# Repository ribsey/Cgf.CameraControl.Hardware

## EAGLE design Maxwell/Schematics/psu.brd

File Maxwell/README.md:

# Maxwell MP-101 electronics replacement
## Specifications
With this replacement your Maxwell PTZ head can do the following:
* smoother movement on low speeds (designed for moving while live)
* positioning
* VISCA control input
* LANC output
* variable power output for camera
* USB power output for HDMI to SDI converters (e.g. BlackmagicDesign Micro Converter HDMI to SDI)

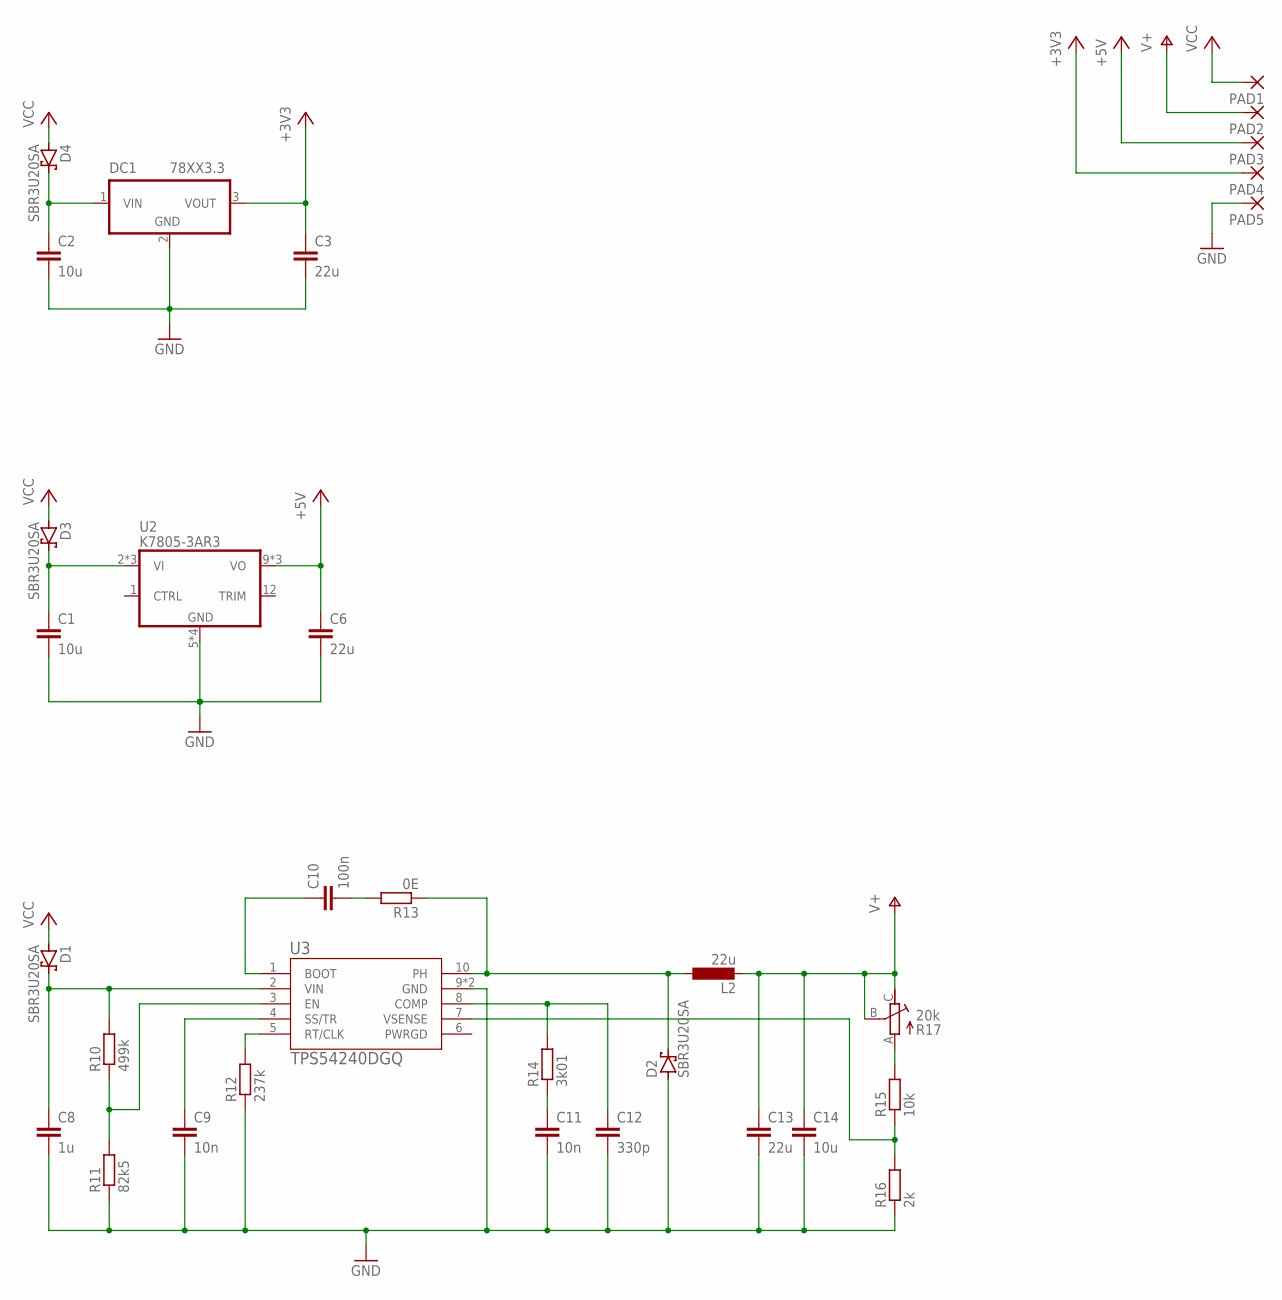
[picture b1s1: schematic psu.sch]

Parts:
C1, C2: 10u; C0805
C3, C6, C13: 22u; C0805
C8: 1u; C0805
C9, C11: 10n; C0603
C10: 100n; C0603
C12: 330p; C0603
C14: 10u; C0603
D1, D2, D3, D4: SBR3U20SA; SMA
DC1: 78XX3.3; SIP3
L2: 22u; ETQP4M
PAD1, PAD2, PAD3, PAD4, PAD5: WIREPAD2,54/1,1; 2,54/1,1
R10: 499k; R0603
R11: 82k5; R0603
R12: 237k; R0603
R13: 0E; R0603
R14: 3k01; R0603
R15: 10k; R0603
R16: 2k; R0603
R17: 20k; TS53YL
U2: K7805-3AR3; K78XX-3AR3
U3: TPS54240DGQ; HVSSOP-10P

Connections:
+3V3: C3.1, DC1.3 (VOUT), PAD4.1
+5V: C6.1, PAD3.1, U2.9 (VO), U2.10 (VO), U2.11 (VO)
GND: C1.2, C2.2, C3.2, C6.2, C8.2, C9.2, C11.2, C12.2, C13.2, C14.2, D2.A, DC1.2 (GND), PAD5.1, R11.1, R12.1, R16.1, U2.5 (GND), U2.6 (GND), U2.7 (GND), U2.8 (GND), U3.9 (GND), U3.11 (GND)
unnamed: C8.1, D1.C, R10.2, U3.2 (VIN)
unnamed: C1.1, D3.C, U2.2 (VI), U2.3 (VI), U2.4 (VI)
unnamed: C2.1, D4.C, DC1.1 (VIN)
unnamed: C11.1, R14.1
unnamed: C10.1, U3.1 (BOOT)
unnamed: C10.2, R13.2
unnamed: D2.C, L2.1, R13.1, U3.10 (PH)
unnamed: R15.1, R16.2, U3.7 (VSENSE)
unnamed: R10.1, R11.2, U3.3 (EN)
unnamed: C9.1, U3.4 (SS/TR)
unnamed: R12.2, U3.5 (RT/CLK)
unnamed: C12.1, R14.2, U3.8 (COMP)
unnamed: R15.2, R17.A
V+: C13.1, C14.1, L2.2, PAD2.1, R17.B (S), R17.C (E)
VCC: D1.A, D3.A, D4.A, PAD1.1

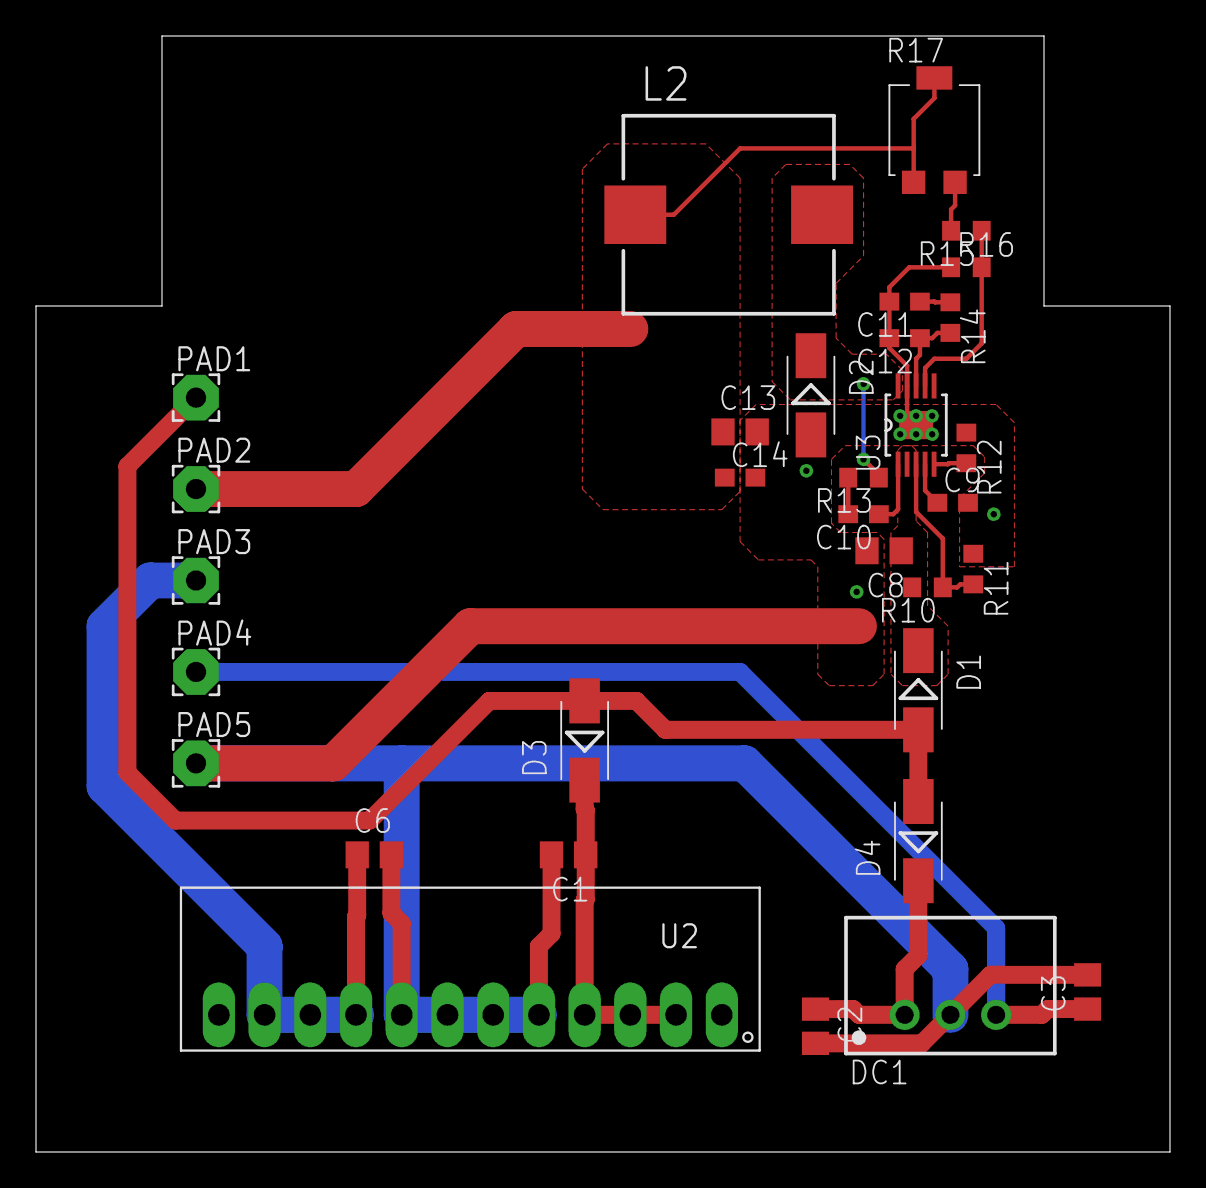
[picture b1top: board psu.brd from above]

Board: 2 copper layers, 63.0 x 62.0 mm, 32 parts (0 on the bottom side), 18 nets.

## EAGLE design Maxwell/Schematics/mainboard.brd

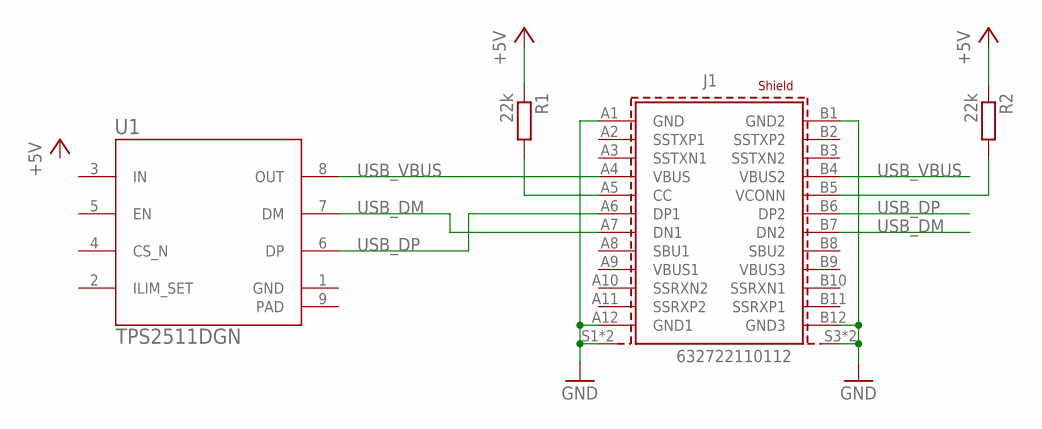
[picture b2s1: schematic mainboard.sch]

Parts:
J1: 632722110112
R1, R2: 22k; R0603
U1: TPS2511DGN; VSSOP-8P

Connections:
+5V: R1.1, R2.1
GND: J1.A1 (GND), J1.A12 (GND1), J1.B1 (GND2), J1.B12 (GND3), J1.S1 (SHIELD), J1.S2 (SHIELD), J1.S3 (SHIELD1), J1.S4 (SHIELD1), U1.1 (GND)
IN: U1.3 (IN)
unnamed: J1.A5 (CC), R1.2
unnamed: J1.B5 (VCONN), R2.2
PAD: U1.9 (PAD)
USB_DM: J1.A7 (DN1), J1.B7 (DN2), U1.7 (DM)
USB_DP: J1.A6 (DP1), J1.B6 (DP2), U1.6 (DP)
USB_VBUS: J1.A4 (VBUS), J1.B4 (VBUS2), U1.8 (OUT)

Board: 2 copper layers, 4 parts (0 on the bottom side), 7 nets, no tracks yet.

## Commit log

2021-02-10 initial commit
    datasheets, eagle project
2021-04-06 prepared files, PSU nearly finished

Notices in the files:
parts and their libraries:
Wurth_Connectors_WR-USB: Copyright: Würth Elektronik
